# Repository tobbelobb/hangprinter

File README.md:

Hangprinter 
===========

Welcome to the Hangprinter repository!

This branch contains Hangprinter version 4.
Breaking changes might occur from time to time.

For more general information about the Hangprinter Project, refer to [hangprinter.org](https://hangprinter.org).

Documentation
----------------
Start here: [hangprinter.org/doc/v4](https://hangprinter.org/doc/v4/).

Getting the source files
-----------------------
Install Git, then clone with submodules so the BOSL2 OpenSCAD library is included:

```sh
git clone --recurse-submodules https://gitlab.com/tobben/hangprinter.git
cd hangprinter
```

If you already cloned without `--recurse-submodules`, run this inside the repository:

```sh
git submodule update --init --recursive
```

`make setup` runs the same command. It downloads the library version recorded in
this repository and needs an internet connection the first time. After pulling
updates or switching branches, run it again to keep the library in sync.

GitLab/GitHub source ZIP downloads omit submodules. Use the Git clone above for
editing CAD. The models expect BOSL2 at `src/lib/BOSL2/`; installing it only in
OpenSCAD's global library directory won't fill that path.

Opening and building CAD
------------------------
Install OpenSCAD 2021.01 or later. Open a `.scad` file from `src/` in OpenSCAD,
preview it, then render and export it as STL. The RefWinch models live in
`src/refwinch/`, including `conventional_winch.scad`.

For command-line builds, install GNU Make and put `openscad` on your PATH.
On macOS, the Makefile uses `/Applications/OpenSCAD.app/Contents/MacOS/OpenSCAD`.
Run these commands from the repository root:

```sh
make check-deps
make spool.stl
```

The STL is written to `stl/spool.stl`. To use another OpenSCAD installation,
pass its executable path, for example:

```sh
make check-deps OPENSCAD_BIN=/path/to/openscad
make spool.stl OPENSCAD_BIN=/path/to/openscad
```

Models in subdirectories use the matching output path, for example
`make stl/refwinch/conventional_winch.stl`.

If OpenSCAD says it can't open `BOSL2/std.scad`, or reports unknown BOSL2
functions or modules, run `git submodule update --init --recursive` and preview
the model again. `make` checks for the library and required programs before building.

Using letter sized paper for the layout?
-------------------------
You can specify that in a make-call:
```
make layout_letter.pdf
```

Layout PDFs also require CairoSVG (the `cairosvg` command), sed, and Ghostscript
(the `gs` command). Check them with `make check-layout-deps`.
`make all` builds both the STLs and the A4 layout PDF, so it needs these programs too.

Contributing Improvements
-------------------------
We're super grateful for merge request.
Please submit to this repo on Gitlab.

The second best option for contributing improvements is to make an issue on Gitlab.

Lead Dev
---------------------------------
[tobben](https://torbjornludvigsen.com).

Campaign
---------------------------------
[Github Sponsors](https://github.com/sponsors/tobbelobb/)

Merchandise
---------------------------------
[Spreadshirt link for Sweden](https://shop.spreadshirt.se/hangprinter-merchandise/).
[Spreadshirt link for US](https://shop.spreadshirt.com/hangprinter-merchandise/).

Credits
-------
See [contributors](https://gitlab.com/tobben/hangprinter/graphs/version_4) for committer stats.
Note that almost all ideas implemented by the commits have come up in conversations among fellow Reprappers.
Thanks!

List sorted alphabetically.

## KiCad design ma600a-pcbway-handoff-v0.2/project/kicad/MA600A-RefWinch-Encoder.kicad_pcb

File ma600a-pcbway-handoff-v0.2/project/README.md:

# MA600A RefWinch Encoder

A small magnetic incremental encoder board for the Hangprinter RefWinch odometer.

**Status:** v0.3 KiCad schematic, routed PCB and five-board first-article manufacturing package completed. Start with [ordering instructions](release/ORDER-INSTRUCTIONS.md) and [design review](release/Design-review.md). KiCad 10.0.6 native ERC, DRC and schematic parity pass with zero findings; 182 independent checks pass. Physical first-article validation remains. No order has been placed.

**Applicable RefWinch variants:** buildup and no-buildup. The board measures the odometer wheel, independent of collector-spool architecture.

## Design goal

A cheap, keyed, no-MCU magnetic encoder board that can plug into a motor controller such as CLN17 and output native A/B/Z quadrature.

## Architecture

```text
JST-GH 6-pin
5 V ────────┐
            │   MP20056GJ-33
            └──► 3.3 V LDO ─────────┐
GND ───────────────────────────────┐ │
                                   │ │
                             ┌─────▼─▼─────┐
                             │   MA600A    │
                             │             │
                        A ◄──┤ IO2         │
                        B ◄──┤ IO4         │
                        Z ◄──┤ IO3         │
                             │             │
SPI pogo pads: /CS,SCLK,COPI,CIPO         │
                             └─────────────┘
```

## Main connector

J1: JST-GH 6-pin, right-angle, `SM06B-GHS-TB(LF)(SN)`.

| Pin | Signal | Direction | Notes |
|---:|---|---|---|
| 1 | GND | power | 0 V |
| 2 | +5V | input | nominal 5 V from controller |
| 3 | A | output | 3.3 V push-pull quadrature A |
| 4 | B | output | 3.3 V push-pull quadrature B |
| 5 | Z | output | 3.3 V push-pull index |
| 6 | RSV | — | no-connect in v0.1 |

Using our own connector makes the sensor PCB independent of CLN17-V3 connector revisions. The CLN17 end is handled by a cable mapping.

## Default behavior

The MA600A factory-default interface maps IO2=A, IO4=B, IO3=Z. Factory-default quadrature resolution is 512 pulses/rev (2048 edges/rev), so the board works without configuration. Resolution can later be stored in the MA600A NVM from 1 to 4096 pulses/rev.

## Magnetic-layout rule

The MA600A sits at the **tip of the PCB**. All capacitors, regulator, connector, mounting holes, and test pads are kept at least 5 mm from the sensor center; v0.1 targets 6 mm or more. No ground pour is planned inside the magnetic keepout except the minimum traces required by the sensor.

This is unusually important: MPS documents measurable magnetic distortion from nearby SMD capacitors and recommends at least 5 mm distance.

## Power

The MA600A requires 3.3 V. The board therefore uses an `MP20056GJ-33` low-noise LDO from the 5 V encoder supply.

- C1: 2.2 uF LDO input bypass
- C2: 4.7 uF LDO output bypass
- C3: 1 uF MA600A AVDD bypass
- C4: 0.1 uF MA600A DVDD bypass
- LDO EN tied to VIN
- LDO FB left open for the fixed 3.3 V version

## Project layout

- `hardware/` — netlist, pinout, placement drawing, schematic drawing
- `manufacturing/` — BOM, draft centroid, assembly notes
- `programming/` — SPI/NVM plan
- `validation/` — checks before any production order
- `docs/` — design decisions and source notes

## Current deliverables and remaining validation

- `kicad/` — editable, self-contained KiCad sources and local libraries.
- `release/` — Gerber ZIP, BOM, centroid, schematic and assembly PDFs, verification reports, and order instructions.
- `tools/` — design-generation and release-verification utilities.
- `analysis/` — detailed machine-readable review evidence and run manifest.

The original `hardware/`, `manufacturing/` and `docs/` material is retained as design history; use the v0.3 release for manufacturing. Order five first articles through normal PCB fabrication and assembly, then perform the electrical, cable and actual magnet-geometry tests. Larger runs remain gated on physical validation.

## Primary references

- MPS MA600A datasheet: https://www.monolithicpower.com/en/documentview/productdocument/index/version/2/document_type/Datasheet/lang/EN/sku/MA600A
- MPS MP20056 datasheet: https://www.monolithicpower.com/en/documentview/productdocument/index/version/2/document_type/Datasheet/lang/en/sku/MP20056/
- Chinese MA600A + MP20056GJ reference project: https://oshwhub.com/mps-core-source-square/ma600a-mp20056gj
- Project-structure benchmark (not circuit source): https://github.com/Westly-Bouchard/AS5047P-Board

## License

Not selected yet. Choose an open-hardware license before publishing the repository.

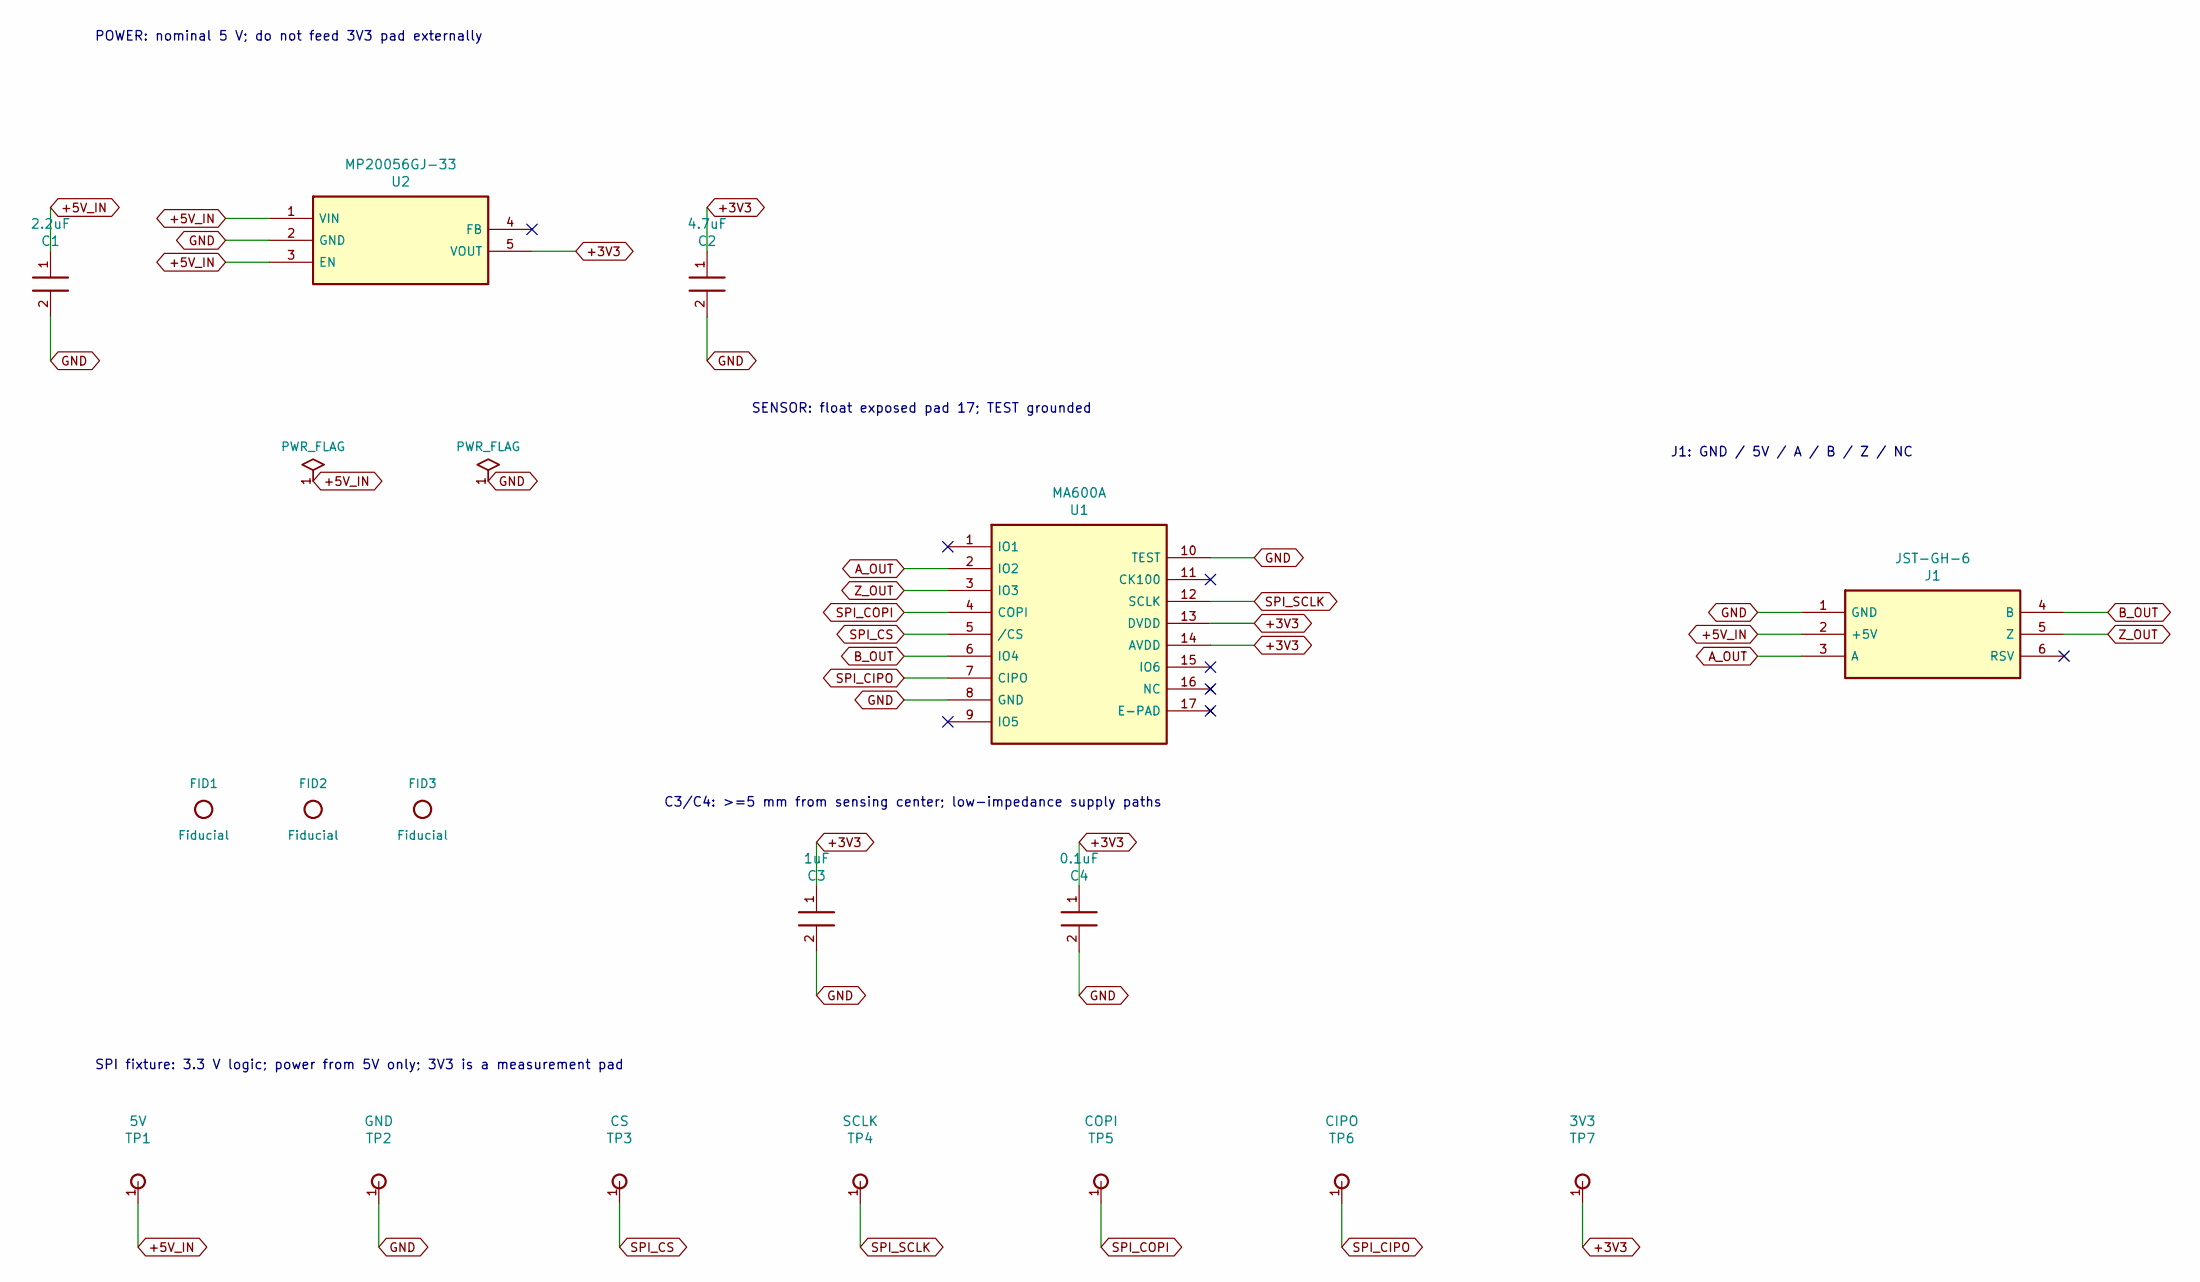
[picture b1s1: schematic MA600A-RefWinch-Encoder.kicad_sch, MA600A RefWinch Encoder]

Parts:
C1: 2.2uF; C_0603_1608Metric; MPN GRM188R71A225KE15D
C2: 4.7uF; C_0603_1608Metric; MPN GRM188Z71A475KE15D
C3: 1uF; C_0402_1005Metric; MPN GRM155Z71A105KE01D
C4: 0.1uF; C_0402_1005Metric; MPN GRM155R71C104KA88D
FID1, FID2, FID3: Fiducial; Fiducial_0.6mm_Mask1.1mm
J1: JST-GH-6; JST_GH_SM06B-GHS-TB_1x06-1MP_P1.25mm_Horizontal; MPN SM06B-GHS-TB(LF)(SN)
TP1: 5V; Pogo_1mm
TP2: GND; Pogo_1mm
TP3: CS; Pogo_1mm
TP4: SCLK; Pogo_1mm
TP5: COPI; Pogo_1mm
TP6: CIPO; Pogo_1mm
TP7: 3V3; Pogo_1mm
U1: MA600A; MA600A_QFN16_3x3_EP1.7; MPN MA600AGQE-0000-Z
U2: MP20056GJ-33; MP20056_TSOT23_5; MPN MP20056GJ-33-Z

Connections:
+3V3: C2.1, C3.1, C4.1, TP7.1, U1.13 (DVDD), U1.14 (AVDD), U2.5 (VOUT)
+5V_IN: C1.1, J1.2 (+5V), TP1.1, U2.1 (VIN), U2.3 (EN)
A_OUT: J1.3 (A), U1.2 (IO2)
B_OUT: J1.4 (B), U1.6 (IO4)
GND: C1.2, C2.2, C3.2, C4.2, J1.1 (GND), TP2.1, U1.8 (GND), U1.10 (TEST), U2.2 (GND)
SPI_CIPO: TP6.1, U1.7 (CIPO)
SPI_COPI: TP5.1, U1.4 (COPI)
SPI_CS: TP3.1, U1.5 (/CS)
SPI_SCLK: TP4.1, U1.12 (SCLK)
Z_OUT: J1.5 (Z), U1.3 (IO3)

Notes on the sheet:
POWER: nominal 5 V; do not feed 3V3 pad externally
SENSOR: float exposed pad 17; TEST grounded
J1: GND / 5V / A / B / Z / NC
C3/C4: >=5 mm from sensing center; low-impedance supply paths
SPI fixture: 3.3 V logic; power from 5V only; 3V3 is a measurement pad

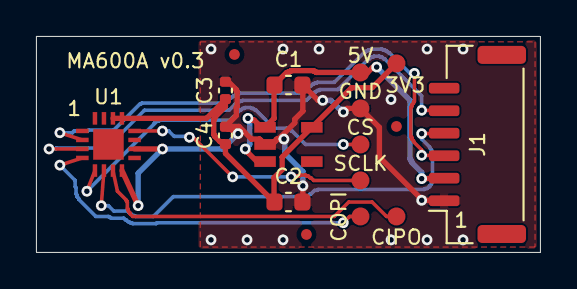
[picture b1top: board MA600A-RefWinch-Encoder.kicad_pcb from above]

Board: 2 copper layers, 28.0 x 12.0 mm, 17 parts (0 on the bottom side), 10 nets.

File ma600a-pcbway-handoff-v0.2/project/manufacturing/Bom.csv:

Item #;Designator;Quantity;Manufacturer;Mfg Part #;Description / Value;Package / Footprint;Notes
1;U1;1;Monolithic Power Systems;MA600AGQE-0000-Z;Magnetic angle sensor;QFN-16 3x3 wettable flank;Factory-default configuration
2;U2;1;Monolithic Power Systems;MP20056GJ-33-Z;3.3V low-noise LDO;TSOT23-5;Fixed 3.3V
3;J1;1;JST;SM06B-GHS-TB(LF)(SN);6-pin keyed right-angle connector;JST GH 1.25mm;Mating housing GHR-06V-S
4;C1;1;ANY;TBD;2.2uF 10V X7R;0603;LDO input bypass
5;C2;1;ANY;TBD;4.7uF 10V X7R;0603;LDO output bypass
6;C3;1;ANY;TBD;1uF 10V X7R;0402;MA600A AVDD bypass
7;C4;1;ANY;TBD;0.1uF 16V X7R;0402;MA600A DVDD bypass

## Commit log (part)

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2021-05-25 Increases spool radius
    ... as well as many other little adjustments for the HP4 prototype 2
2021-05-25 Adds spool cover stls
2021-05-26 Adjusts whitelabel motor screw hole positions
2021-05-26 Some reorganization of motor bracket code
2021-05-26 Makes space to remove idler from spool cores while mounted
2021-05-27 Redid tilted line deflector again
2021-05-27 Fixes BC line placements
2021-05-31 Removes donkey from Makefile
2021-05-31 Prepares line verticalized for 4x mechanical advantage
2021-05-31 Tidies up motor bracket source
2021-05-31 Prepares roller walls for smooth rod inserts
2021-05-31 Adds mirrored version of tilted line deflector
2021-05-31 Renames beam_slider_D to ziptie_tensioner_wedge
2021-05-31 Marks motor brackets with ABCD letters
2021-06-01 Adds 4x mech adv for D, and eyelets for ABC lines
2021-06-01 Adds nutlock to brace tightener
2021-06-01 Makes make all work again and updates all outputs
2021-06-02 Minor adjustments to spool core. Places out smooth rods in render
2021-06-02 Fixes yet another bug on the corner clamp
2021-06-02 Put a vgroove dress on your flat old 623 bearing!
2021-06-03 Moves landing brackets to a more practical position
2021-06-03 Cosmetic fix
2021-06-03 Prepares for larger bearing and line
2021-06-04 Increases size of teeth in core
2021-06-04 Cosmetic change to spool core foot
2021-06-04 Gives vgroove bearings a little more space
2021-06-04 Updates line verticalizer stl
2021-06-07 Fixes dleft spool cover
2021-06-08 Gives more space for bearings
2021-06-09 Gives bearing and screw head some more space
    ... in the three deflectors
2021-06-10 Enlargens holes for eyelets
2021-06-10 Gets screw hole sizes under control
2021-06-10 Makes belt roller insert smaller
2021-06-10 Updates layout a4 pdf
2021-06-10 Gives more room fore ODrive boards
2021-06-11 Updates layout
2021-06-11 Reduces risk of nagging teeth
2021-06-17 Updates odrive related readme
2021-06-17 Deletes old ODriveFirmware binaries
2021-06-17 Updates config and RRF binary
2021-06-22 Updates odrive config instructions
2021-06-22 Updates M569.3 specification
2021-06-28 Slants bearings in line_roller_double.stl
2021-06-28 Adds preventor edges to line roller double
2021-06-29 Adds RRF binary with M569.2/3 working ok
2021-06-29 Bugfix
2021-06-30 Swaps back mixed up B/C motors
2021-06-30 Changes to get motor directions right
2021-06-30 Bigger eyelets for line verticalizer
2021-07-01 Increases size of a line opening
2021-07-01 Removes minor misplaced blip
2021-07-01 Moves M569.2 to M569.4
2021-07-01 Adds newer line_roller_anchor
2021-07-02 Adds a mirrored version of line_roller_anchor
2021-07-02 Is a bit more forgiving on screw length
2021-07-02 updates stl
2021-07-05 updates stls
2021-07-05 Renames mirrored_spool_cover to spool_cover_mirrored
2021-07-07 Makes sep disc easier to mount right
2021-07-07 Adds new sep disc stl
2021-07-12 Spool cover scad changes for prev commit
2021-07-13 Tighter tolerance for GT2 spool gear
2021-07-14 Fixes minor bug in motor bracket D
2021-07-14 Updates 2d layout with new motor brackets
2021-08-01 Adds extension board bracket
2021-08-16 Makes more space for the belt
2021-08-16 Revert "Makes more space for the belt"
    This reverts commit 2f493cda1c66f11c68d05d3d5514b58c19ae3602.
2021-08-19 Changes directions of all motors
    This is necessary because we changed the CAN addresses in an earlier
    commit.
    Turns out that CAN address change made all motors go backwards when they
    were supposed to go forwards, and vice versa.
2021-08-21 Changes spool radii from ca 65 to ca 75
2021-08-24 Updates special gcodes docs
2021-08-25 Updates README.md
2021-08-25 Adds ODrives to layout.scad
2021-08-25 Adds some useful macros
2021-08-27 Minor changes to brace tightener
2021-08-31 Sets print accel low but travel accel high
2021-09-01 Removes sharp bottom from bearing v
2021-09-02 Adds marker stls
2021-09-09 Scales up tilted line deflectors to 608 bearing size
2021-09-14 Converts tilted line deflector to 608 bearing
    This is because we've seen some fraying of the lines
    that rolled over the old version, that used a smaller
    623 bearing.
2021-09-15 Converts line roller double to 608 bearings
2021-09-15 Updates stl/README.md
2021-09-15 Removes old documentation system
2021-09-23 Updates RepRapFirmware binary
2021-09-29 Gives more space for line in tilted line deflector
2021-10-06 Makes bearing u 608 official part of the family
2021-10-13 Yet another tilted line deflector fix
2021-10-13 Adds individual motor control macro
2021-10-18 Extends dspool for wire rewinding
    ... only thing missing is the dright spool cover,
    which is not made yet.
2021-10-19 Makes dright spool top slice in PrusaSlicer
2021-10-19 Adds line roller wire rewinder
    Note: Not integrated into layout.scad.
    So layout_a4.pdf is not up to date yet.
    Makefile is also missing every stl that has to do with wire rewinding.
2021-10-20 Moves line roller a little bit further from spool
2021-10-21 Improves tolerances for dright spool bearing
2021-10-28 Updates ODrive config
2021-10-28 Disables ODrive heartbeat
2021-11-01 Adds accel and decel limits to ODrive config
2021-11-06 Adds pen holder
    Heavily inspired by Tech2C's 1_Axis_Pen_Holder.stl found here:
    https://www.thingiverse.com/thing:2459624/files
    Re-implemented in Openscad.
    Doubled y-length and added Nema17 attachment to match Hangprinter
    bracket.
    Adds studs at bottom to help adjust rubber band length, and to stabilize
2021-11-08 Removes accel limit and decel limit
    ... because they are only relevant in trapezoidal velocity mode, which
    we don't use.
2021-11-10 Adds bltouch stuff
2021-11-10 Adds comments on bltouch installation
2021-11-16 Makes brace tightener a bit more practical
2021-11-17 Makes some nut sinks in bltouch arm
2021-11-17 Adds bltouch arm to match with flying pen setup
2021-11-18 Minor adjustment to pen fly brace
2021-11-23 Changes dimensions of bltouch arm
2021-11-29 Makes tilted line deflector line cutouts
2021-11-29 Minor changes to odrive config
2021-12-07 Increases width of bearing u by 0.5 mm
2021-12-07 Fixes mirrored line deflector angle
2021-12-07 Reduces width of bearing u again by 0.3 mm
2021-12-20 Lowers acceleration for travel moves
2021-12-22 Adds encoder stabilizer in openscad
    ... not yet included in stl and layout_a4.pdf.
    Needs to be printed and tested first.
2022-01-12 Gives a tiny bit more space for belt roller insert
2022-01-13 More sturdy screw holes for motor
2022-01-13 Makes larger hole in spool legs for core
2022-01-13 Updates motor bracket stls
2022-01-20 Makes GT2 spool gear a tiny bit easier to mount
2022-01-20 Makes spool cover a tiny bit easier to mount
2022-01-21 Adds odrive config dumps
2022-01-21 Commends on ODrive backup config dumps
2022-01-21 Uses big ugroove in line verticalizer
2022-01-26 Cleans up 623 vgroove rests
2022-01-27 Fixes fly brace angles
2022-01-29 Tilts bearings more steeply downwards
2022-01-29 Tidies up Makefile
2022-02-09 Updates pi mount
2022-02-21 WIP: Make encoders easier to mount
2022-02-21 Gets stray docs in comments up to date
2022-02-22 Reverts shortening of pi_mount
2022-02-22 Includes some more useful cable clamps
2022-02-24 Improves anticogging calibration instructions
2022-02-24 Removes unused spool cover ears
2022-02-24 Makes spool cover easier to get line through
    ... should make mounting quicker, if the CADded supports work...
2022-03-01 Makes more space for line
    ... because one of the D-lines were squeezed inside one of the
    horizontal line deflectors.
2022-03-01 Increases size of bearing u 608
    ... in order to make it easier to print.
2022-03-08 Adds separate torque mode macros for each motor
2022-03-14 Gives directory structure to torque macros
2022-03-14 Improves support for flex compensation
2022-03-15 More flex comp config changes
2022-03-15 New flex compensating fw binary
2022-03-17 Repairs stls
2022-03-17 Revert "Upgrades default ODriveFirmware to 0.5.4"
    This reverts commit 0052bc2e90c143b63b2291ed234a22992207e328.
2022-03-24 Adds some comments about force measurements
    ... which is an up and coming feature.
    See https://github.com/Duet3D/RepRapFirmware/pull/564
2022-04-05 Indents the ODrive backup configs
2022-04-08 Adds belts to rendering
2022-04-08 Adds more line-containing walls to spool cover
2022-04-20 visualizes data collection
2022-04-21 Adds some more data
2022-05-13 Reduces circular range to work around bug
2022-05-13 Reduces range from 10000 to 1000
2022-05-13 Adds formatted version of config
2022-05-13 Updates ODriveFirmware hex
2022-05-13 Updrives ODrive hex to support force readings
2022-05-13 Finally working motor current readings
2022-05-13 Sets circular_setpoints to true
2022-05-13 Fixes ODriveFirmware settings and custom build
    ... follow this pull request to see when stock ODriveFirmware can be
    used again.
    https://github.com/odriverobotics/ODrive/pull/680
2022-05-13 Sets motor.config.pre_calibrated to false by default
2022-05-16 Adds new tilted line deflector experimental src
2022-05-18 Switch completely to new tilted line deflector
2022-05-18 Starts working on new snails
    Same style as the new tilted line deflectors.
2022-05-19 Gives bearing on snail a rotational axis
2022-05-20 Adds a snail slit insert
2022-05-20 Removes double brace tightener from repo
2022-05-20 Adds clay extruder holder
2022-09-21 Updates ODriveFirmware to 0.5.5
2022-09-21 Adds missing stls
2022-09-21 Makes motor bracket not rely on motor face's edge
2022-09-21 Updates gitignore
2022-12-19 Fixes mirroring of dright_spool_top.stl
2023-06-05 Adds Wasp_extruder_xl30 and some holder parts
2023-06-09 Adds simple rotating bottom and top holders
    ... for Wasp xl30 extruder, based on thrust bearings.
2023-09-20 Changes from 6mm to 4mm nozzle
    Also adds source for the CFS cable mounter part.
2023-09-20 Four low anchors in render
2023-09-20 Final render for blog post
2023-10-17 Updates sketch of reciprocating line guide
2023-10-18 WIP: breaks layout into several files.
    TODO: Attach BCDI lines to their respective placed_winch_unit
2023-10-23 Some tidying and renaming
2023-10-23 Adds motor bracket I
2023-10-23 Some more tidying
2023-10-25 Updates line_roller_anchor.stl
2023-10-25 Adds lines from top unit to anchors
2025-01-14 Reduced buildup compensation to reflect change from 1.1 mm line (Garda) to 0.87 mm line (DC Pro 161)
2026-04-10 Changes "torque mode" to "force mode" in M569.4 docs
2026-04-13 Allow M569.4 to only specify one T for all P
2026-05-20 v1 of refrig design document
2026-05-20 v2 of refrig design document
2026-05-26 Add BOSL2 OpenSCAD mechanical library
2026-05-26 Adds the start of a refwinch
2026-05-27 Fixes dimension bugs on split winch
2026-06-03 Renames split winch to spline winch
2026-06-03 Starts the capstan drive design
2026-06-08 Renames and improves capstan_drive -> traction_collector_winch
2026-06-08 Some more work on the traction_collector
2026-06-09 Minor changes to motor_drive_capstan
2026-06-10 Adds shaft_rotated_eyelet_holder2 to traction collector legs
2026-06-10 Shortens variable names
2026-06-17 First version of self-reversing threaded rod
2026-06-17 A thicker self-reversing threaded rod
2026-06-17 Bigger pawl
2026-06-17 Making grooves steeper
2026-06-17 Revert "Making grooves steeper"
    This reverts commit a30bb0582c693706de940d94eefca17fd9f41a17.
2026-06-17 Pawl for Self reversing screw even thicker and steeper track
2026-06-17 Huge follower
2026-06-17 Adjustments to pawl
